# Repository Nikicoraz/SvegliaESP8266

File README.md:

# Sveglia ESP8266
Questa è una sveglia progettata da zero da me

### Firmware
Il firmware della sveglia è scritto in Arduino

### Hardware
L'hardware della sveglia è composto da un ESP8266, un buzzer polarizzato con un passo di 6.6mm, un display LCD 16x4 con un adattatore da parallelo a seriale I2C, un encoder e un alimentatore

### Progettazione hardware
La progettazione dell'hardware è stata svolta nel software KiCad

### Schematica

### PCB

Per la stampa del PCB ho utilizzato il sito [PCBWay](https://www.pcbway.com/)
### Creazione della sveglia
Dopo aver acquisito i componenti necessari e il circuito stampato, serve creare un file include/secrets.h dove bisogna inserire l'SSID e la password del Wifi e dell'hotspot e flashare l'ESP

Es.
```C
// include/secrets.h

#define SECRET_SSID "<SSID>";
#define SECRET_PASSWD "<Password>";
#define AP_PASSWD "<Password>"
```

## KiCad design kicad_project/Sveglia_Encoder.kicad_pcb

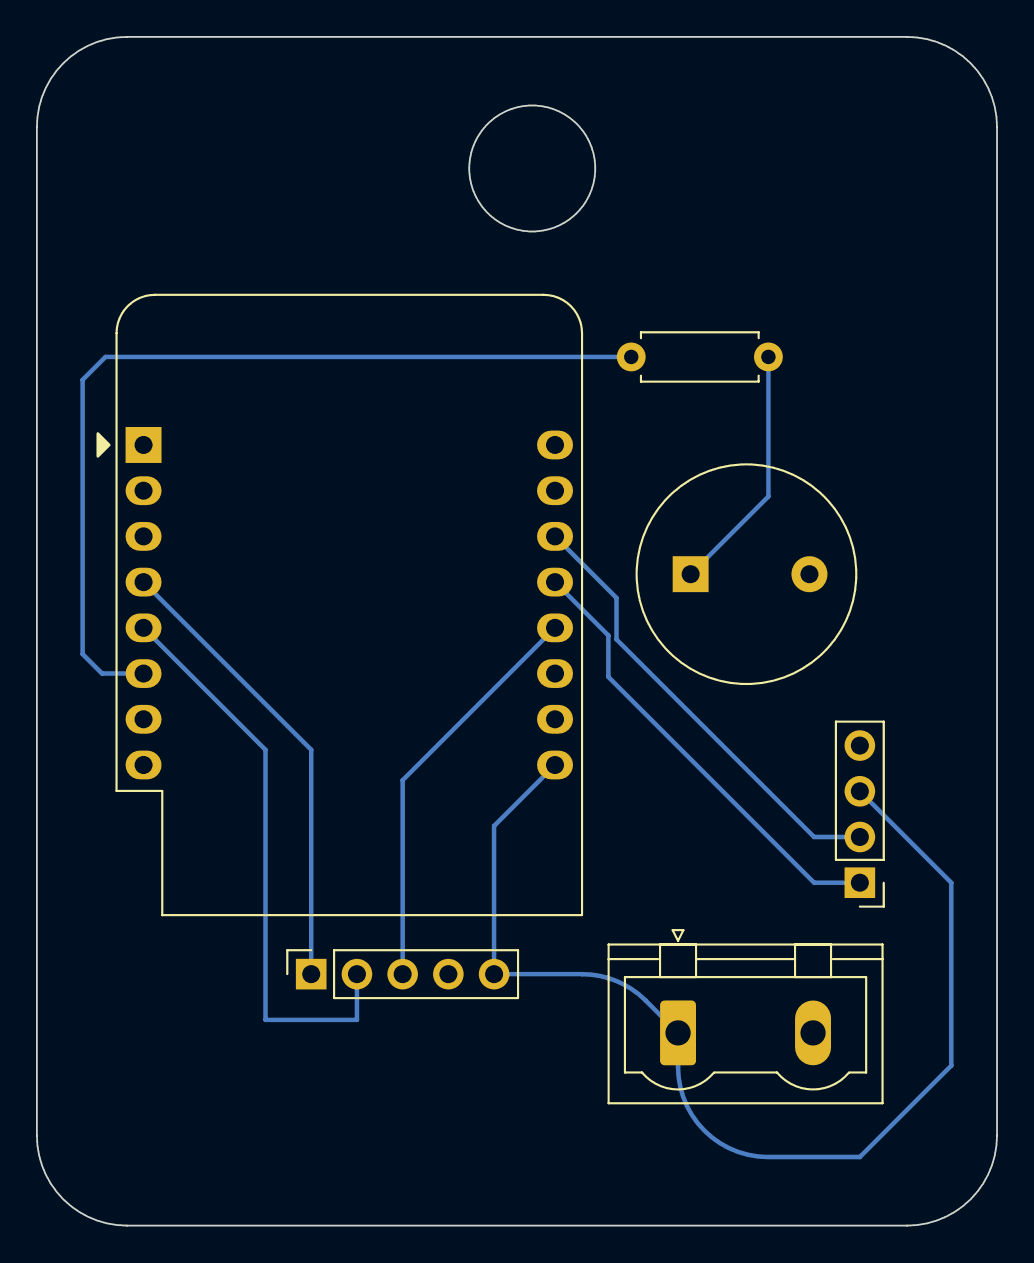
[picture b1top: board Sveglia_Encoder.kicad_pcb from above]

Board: 2 copper layers, 53.3 x 66.0 mm, 6 parts (0 on the bottom side), 9 nets.

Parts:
+5V: PINHD_1x2_Male; PhoenixContact_GMSTBVA_2,5_2-G_1x02_P7.50mm_Vertical
BZ1: Buzzer; Buzzer_12x9.5RM6.6
Display: Display; PinHeader_1x04_P2.54mm_Vertical
R: 270; R_Axial_DIN0207_L6.3mm_D2.5mm_P7.62mm_Horizontal
RotaryEncoder: PinSocket_1x05_P2.54mm_Vertical
Wemos D1 Mini: WeMos_D1_mini; WEMOS_D1_mini_light

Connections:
+5V: +5V.1, Display.3, RotaryEncoder.5 (+), Wemos D1 Mini.9 (5V)
/Buzzer: R.1, Wemos D1 Mini.6 (MOSI/D7)
/DisplaySCL: Display.1, Wemos D1 Mini.14 (SCL/D1)
/DisplaySDA: Display.2, Wemos D1 Mini.13 (SDA/D2)
GNDREF: +5V.2, BZ1.2 (+), Display.4, RotaryEncoder.4 (GND), Wemos D1 Mini.10 (GND)
unnamed: BZ1.1 (-), R.2
unnamed: RotaryEncoder.1 (CLK), Wemos D1 Mini.4 (SCK/D5)
unnamed: RotaryEncoder.2 (DT), Wemos D1 Mini.5 (MISO/D6)
unnamed: RotaryEncoder.3 (SW), Wemos D1 Mini.12 (D3)

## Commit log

2023-11-03 Init
2023-11-04 Encoder
2023-11-04 Rudimental menu
2023-11-08 menu renders now
2023-11-11 Menu scroll
2023-11-11 Update time callback
2023-11-11 Other menu changes
2023-11-29 Selezione orario
2023-11-29 Comments
2023-11-29 Sistemato update che falliva
2023-12-01 Alarm time and save to EEPROM
2023-12-03 Remove alarm option
2023-12-03 Alarm sound
2023-12-08 modify next alarm
2023-12-10 keep wifi connected
2023-12-11 fix next alarm bug
2023-12-11 First menu option bug
2023-12-11 fix next alarm bug again
2023-12-11 Made time more accurate
2023-12-11 Time is more accurate now x2
2023-12-12 Remove LED blink
2023-12-12 Added option to select when the next alarm is (today or tomorrow), next alarm now gets visualized on the display, added option to remove the next alarm
2023-12-16 Rimozione LED
2023-12-16 test alarm button
2023-12-16 Change alarm sound and bug fix
2023-12-16 Simple bug fix
2023-12-16 Save alarm sound to EEPROM and EEPROM initial byte set to 79 to check if the EEPROM has been initialized before
2023-12-16 Alarms can now be interruped during tune
2023-12-16 New alarm sounds
2023-12-16 fix next alarm again
2023-12-18 Oops forgot file
2024-01-22 images
2024-03-03 Stampa PCB
2024-03-16 Update images
2024-03-16 Aggiunte schematiche
2024-03-18 Aggiunta funzionalità OTA
2024-04-02 Legal hour
2024-04-02 next alarm calculation fix
2024-08-05 Possible memory leak
2024-08-05 Fix not valid???
2024-08-05 Test alarm now waits
2025-03-01 EEPROM structure
2025-07-19 Migration to PlatformIO
2025-07-19 mDNS and encoder fix
2025-07-19 webserver initial
2025-07-19 Move .h in include dir
2025-07-20 Added wifi setting webpage
2025-07-20 webserver can now set the wifi ssid and passwd
2025-07-26 new alarm and setupWifi menu option
2025-07-26 readme change
2025-07-28 Modify time manually
